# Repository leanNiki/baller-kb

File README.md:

# THE WIRING IS WRONG, THE TEENSY PINS ARE NOT CORRECT

# baller-kb
Split 50% keyboard with blackberry trackball

## Parts
* 2 PCBs identical
* 1 Blackberry Trackball Breakout Module
* 2 Teensy 2.0
* 60 Mx Blue Switches
* 60 Diodes 1N4148TACT-ND
* 4 5K Resistors (I2C) 4.99KXBK-ND
* 2 Phono Jack TRRS (FC68125)
* ~50 Pin Headers (Teensy) (or wire?)
* TRRS Cable
* Mini USB-Cable
* 60 Switches
* 60 Keycaps
* wire (trackball module)

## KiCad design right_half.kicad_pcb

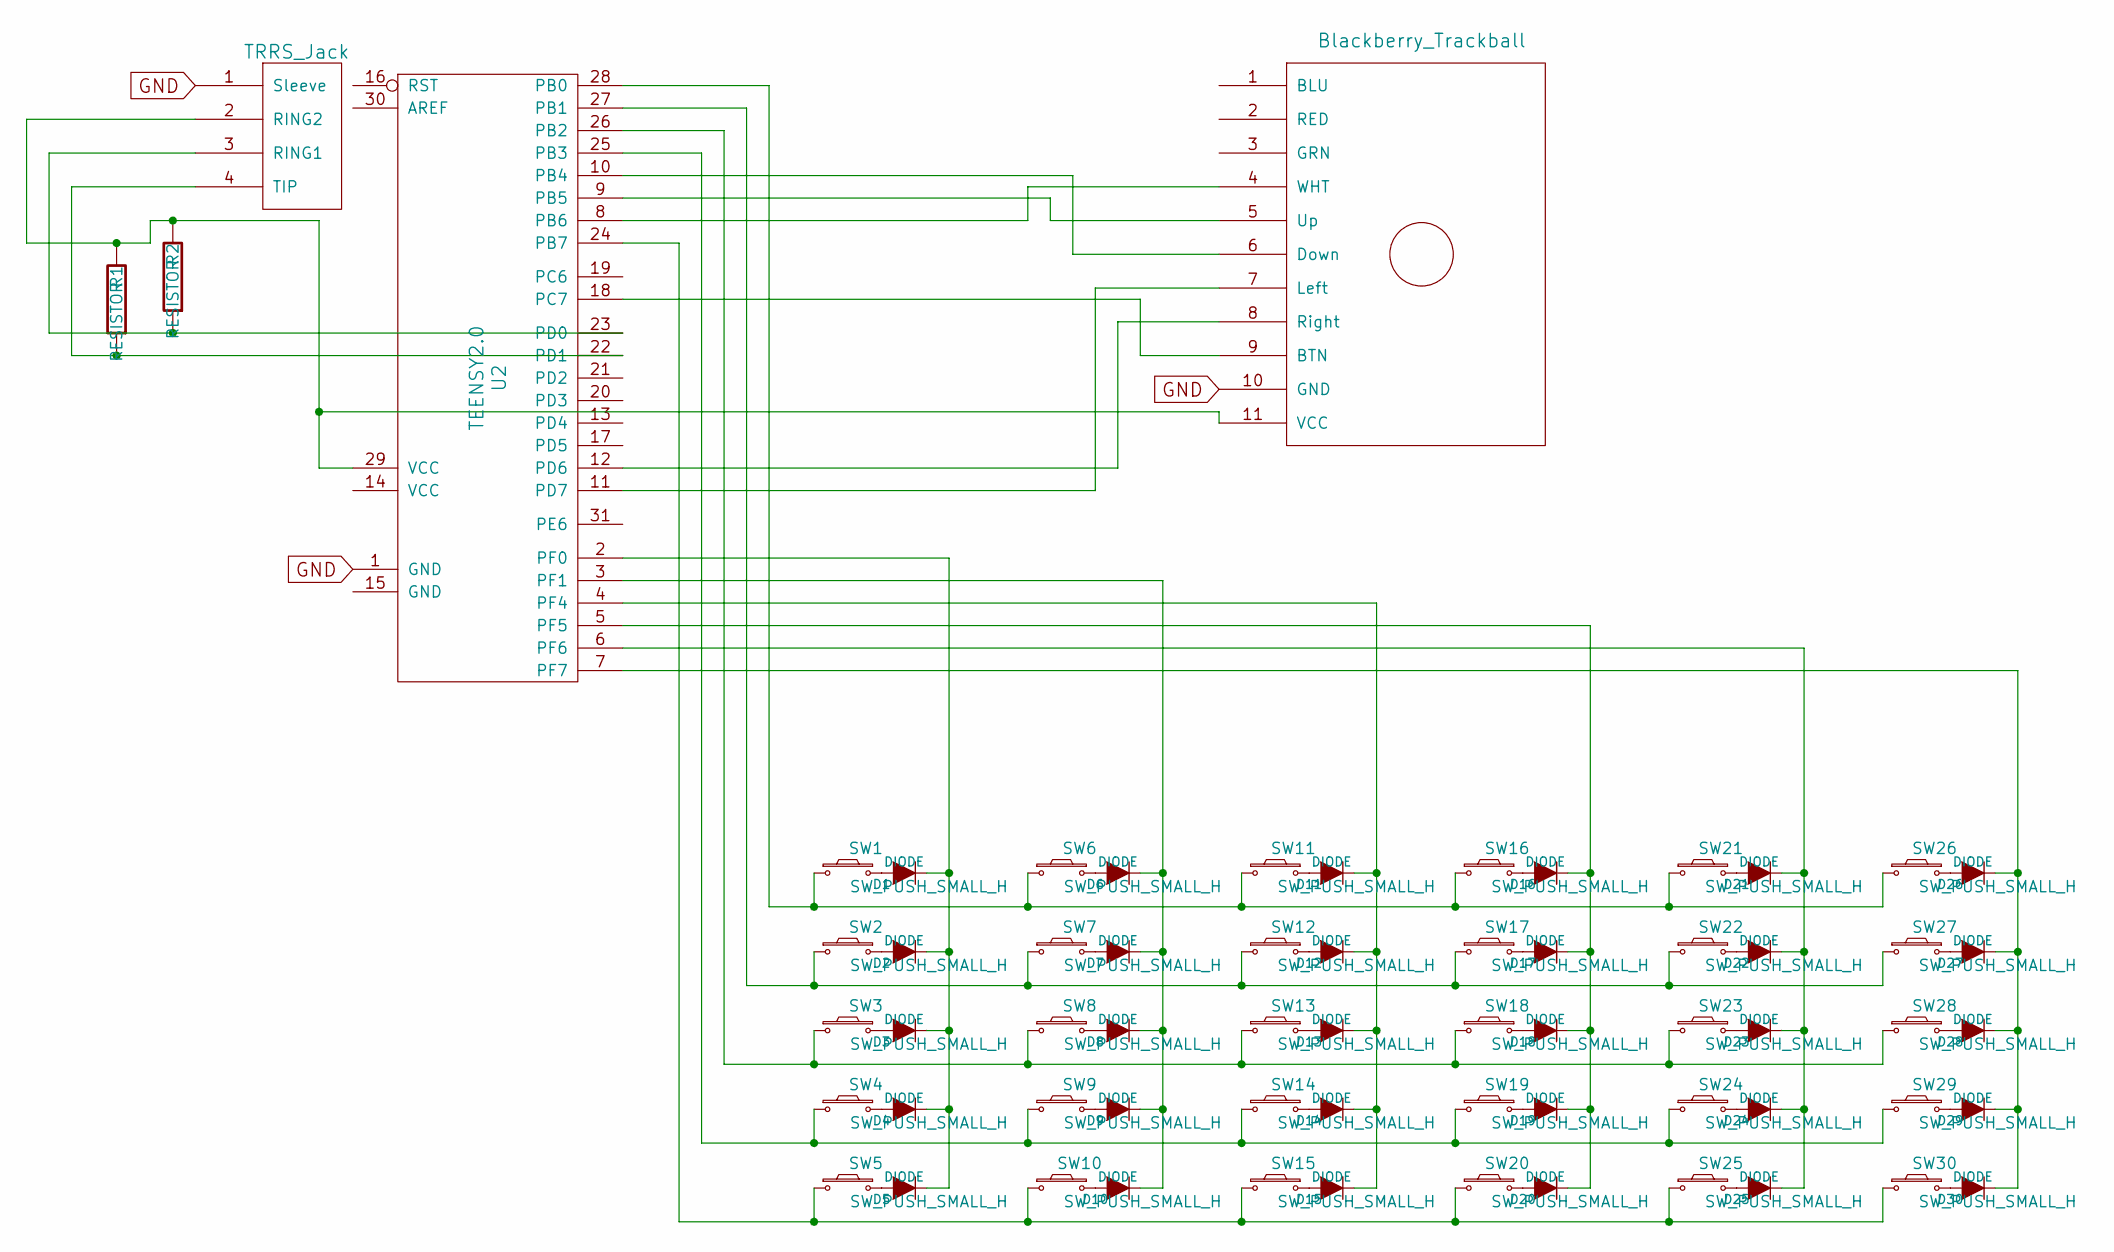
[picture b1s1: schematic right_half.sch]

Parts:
D1, D2, D3, D4, D5, D6, D7, D8, D9, D10, D11, D12, D13, D14, D15, D16, D17, D18, D19, D20, D21, D22, D23, D24, D25, D26, D27, D28, D29, D30: DIODE
R1, R2: RESISTOR
SW1, SW2, SW3, SW4, SW5, SW6, SW7, SW8, SW9, SW10, SW11, SW12, SW13, SW14, SW15, SW16, SW17, SW18, SW19, SW20, SW21, SW22, SW23, SW24, SW25, SW26, SW27, SW28, SW29, SW30: SW_PUSH_SMALL_H; CHERRY_PLATE_100H
U1: TRRS_Jack; trrs_jack
U2: TEENSY2.0; TEENSY_2.0
U3: Blackberry_Trackball; bb_trackball

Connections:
GND: U1.1 (Sleeve), U2.1 (GND), U3.10 (GND)
unnamed: D1.1 (A), SW1.2
unnamed: D1.2 (K), D2.2 (K), D3.2 (K), D4.2 (K), D5.2 (K), U2.2 (PF0)
unnamed: D2.1 (A), SW2.2
unnamed: D3.1 (A), SW3.2
unnamed: D4.1 (A), SW4.2
unnamed: D5.1 (A), SW5.2
unnamed: D6.1 (A), SW6.2
unnamed: D7.1 (A), SW7.2
unnamed: D8.1 (A), SW8.2
unnamed: D9.1 (A), SW9.2
unnamed: D10.1 (A), SW10.2
unnamed: D6.2 (K), D7.2 (K), D8.2 (K), D9.2 (K), D10.2 (K), U2.3 (PF1)
unnamed: D11.1 (A), SW11.2
unnamed: D11.2 (K), D12.2 (K), D13.2 (K), D14.2 (K), D15.2 (K), U2.4 (PF4)
unnamed: D12.1 (A), SW12.2
unnamed: D13.1 (A), SW13.2
unnamed: D14.1 (A), SW14.2
unnamed: D15.1 (A), SW15.2
unnamed: D16.1 (A), SW16.2
unnamed: D16.2 (K), D17.2 (K), D18.2 (K), D19.2 (K), D20.2 (K), U2.5 (PF5)
unnamed: D17.1 (A), SW17.2
unnamed: D18.1 (A), SW18.2
unnamed: D19.1 (A), SW19.2
unnamed: D20.1 (A), SW20.2
unnamed: D21.1 (A), SW21.2
unnamed: D21.2 (K), D22.2 (K), D23.2 (K), D24.2 (K), D25.2 (K), U2.6 (PF6)
unnamed: D22.1 (A), SW22.2
unnamed: D23.1 (A), SW23.2
unnamed: D24.1 (A), SW24.2
unnamed: D25.1 (A), SW25.2
unnamed: D26.1 (A), SW26.2
unnamed: D26.2 (K), D27.2 (K), D28.2 (K), D29.2 (K), D30.2 (K), U2.7 (PF7)
unnamed: D27.1 (A), SW27.2
unnamed: D28.1 (A), SW28.2
unnamed: D29.1 (A), SW29.2
unnamed: D30.1 (A), SW30.2
unnamed: R1.1, U1.4 (TIP), U2.22 (PD1)
unnamed: R1.2, R2.2, U1.2 (RING2), U2.29 (VCC), U3.11 (VCC)
unnamed: R2.1, U1.3 (RING1), U2.23 (PD0)
unnamed: SW1.1, SW6.1, SW11.1, SW16.1, SW21.1, SW26.1, U2.28 (PB0)
unnamed: SW5.1, SW10.1, SW15.1, SW20.1, SW25.1, SW30.1, U2.24 (PB7)
unnamed: SW2.1, SW7.1, SW12.1, SW17.1, SW22.1, SW27.1, U2.27 (PB1)
unnamed: SW3.1, SW8.1, SW13.1, SW18.1, SW23.1, SW28.1, U2.26 (PB2)
unnamed: SW4.1, SW9.1, SW14.1, SW19.1, SW24.1, SW29.1, U2.25 (PB3)
unnamed: U2.8 (PB6), U3.4 (WHT)
unnamed: U2.9 (PB5), U3.5 (Up)
unnamed: U2.10 (PB4), U3.6 (Down)
unnamed: U2.11 (PD7), U3.7 (Left)
unnamed: U2.12 (PD6), U3.8 (Right)
unnamed: U2.18 (PC7), U3.9 (BTN)

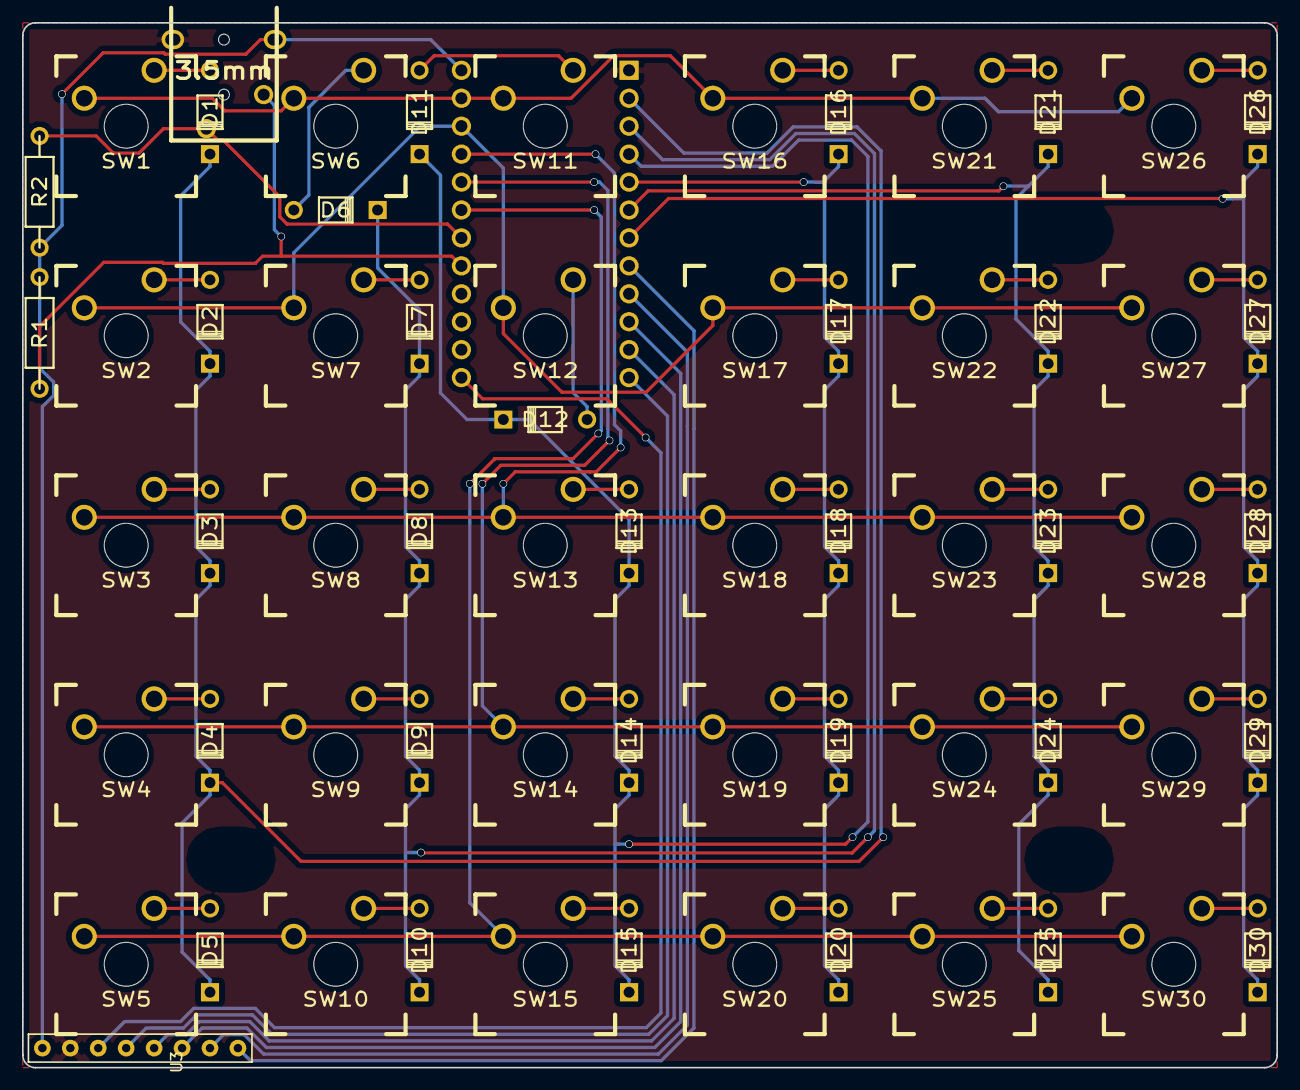
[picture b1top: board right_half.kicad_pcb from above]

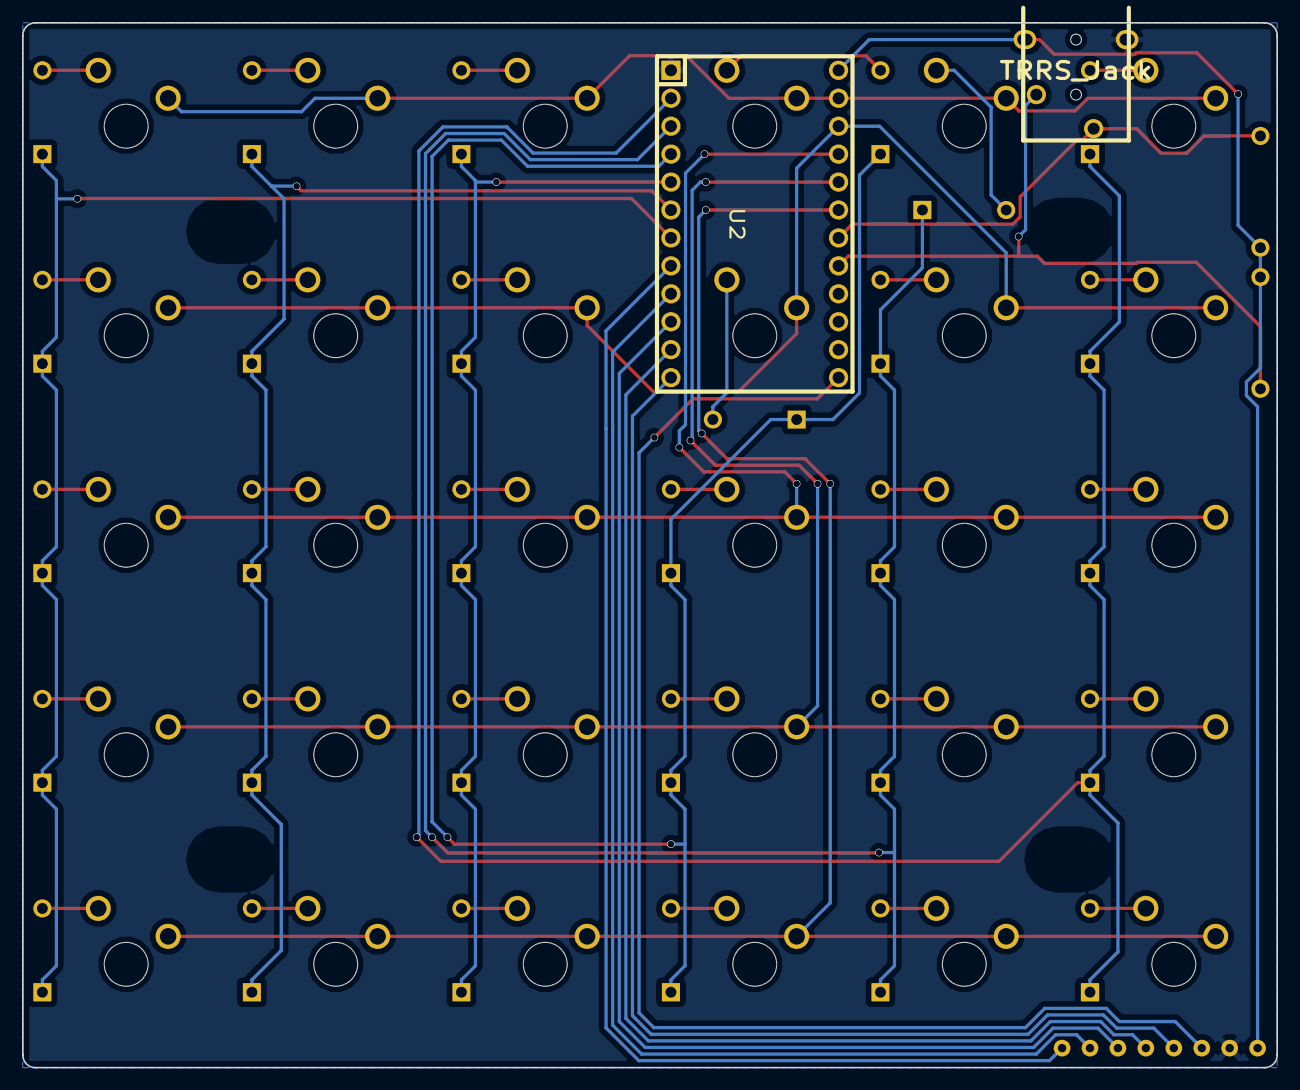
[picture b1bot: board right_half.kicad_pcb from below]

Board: 2 copper layers, 114.0 x 95.0 mm, 69 parts (2 on the bottom side), 51 nets.

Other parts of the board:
REF1, REF2, REF3, REF4: MountingHole_7x5

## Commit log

2018-02-01 added files
2018-08-25 Set theme jekyll-theme-cayman
